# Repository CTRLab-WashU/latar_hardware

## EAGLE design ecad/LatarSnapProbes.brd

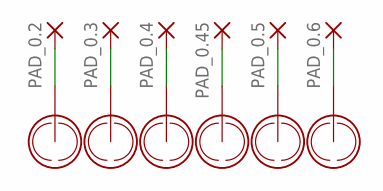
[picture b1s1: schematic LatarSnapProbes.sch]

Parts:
P1: PROBE_0.2_IN
PAD_0.2, PAD_0.3, PAD_0.4, PAD_0.5, PAD_0.6, PAD_0.45: SMD5; SMD2,54-5,08
U$1: PROBE_0.4_IN
U$3: PROBE_0.3_IN
U$4: PROBE_0.45_IN
U$5: PROBE_0.5_IN
U$6: PROBE_0.6_IN

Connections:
unnamed: P1.P1, P1.P2, PAD_0.2.1
unnamed: PAD_0.3.1, U$3.P1, U$3.P2
unnamed: PAD_0.4.1, U$1.P1, U$1.P2
unnamed: PAD_0.45.1, U$4.P1, U$4.P2
unnamed: PAD_0.5.1, U$5.P1, U$5.P2
unnamed: PAD_0.6.1, U$6.P1, U$6.P2

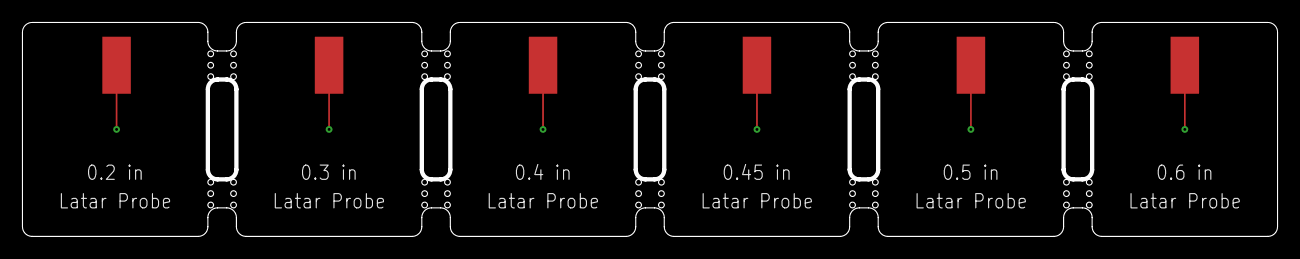
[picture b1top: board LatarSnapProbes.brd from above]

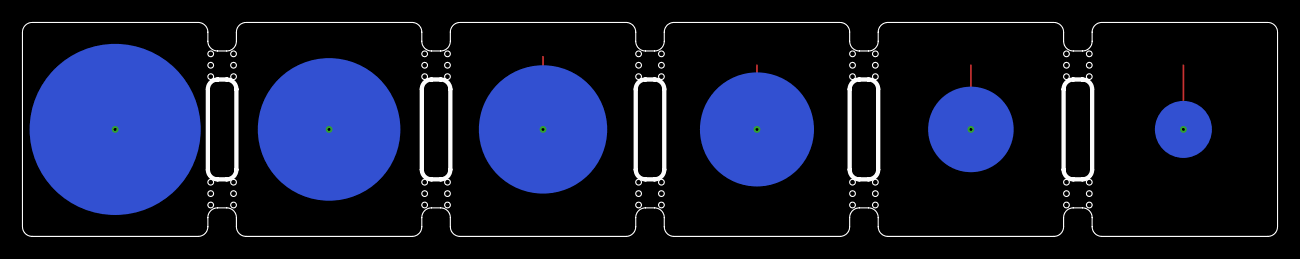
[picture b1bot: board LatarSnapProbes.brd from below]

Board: 2 copper layers, 111.8 x 19.1 mm, 12 parts (6 on the bottom side), 6 nets.

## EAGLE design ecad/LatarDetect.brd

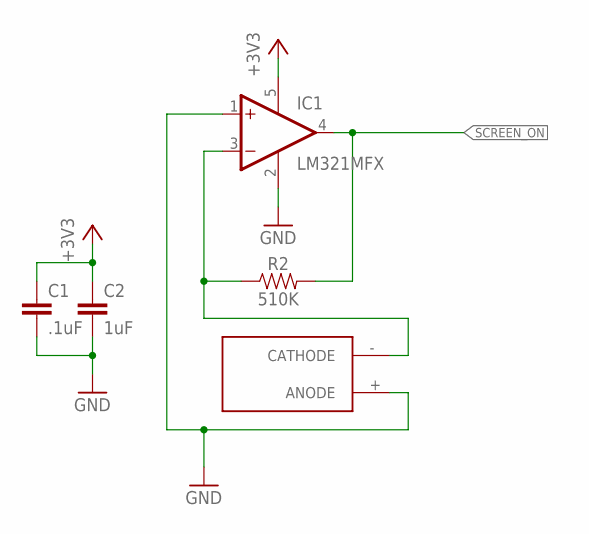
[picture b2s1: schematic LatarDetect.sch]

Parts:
C1: .1uF; C0805
C2: 1uF; C0805
IC1: LM321MFX; SOT23-5
R2: 510K; 0805
U$1: BPW34S-Z

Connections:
+3V3: C1.1, C2.1, IC1.5 (V+)
GND: C1.2, C2.2, IC1.1 (+IN), IC1.2 (V-), U$1.+ (ANODE)
unnamed: IC1.3 (-IN), R2.1, U$1.- (CATHODE)
SCREEN_ON: IC1.4 (OUT), R2.2

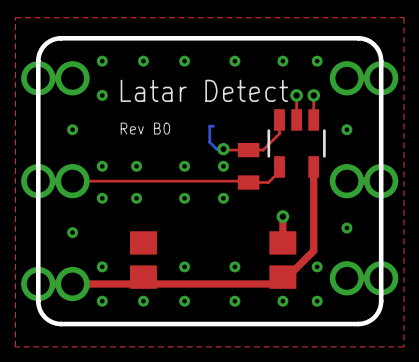
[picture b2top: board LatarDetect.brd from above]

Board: 2 copper layers, 19.1 x 15.9 mm, 5 parts (1 on the bottom side), 4 nets.

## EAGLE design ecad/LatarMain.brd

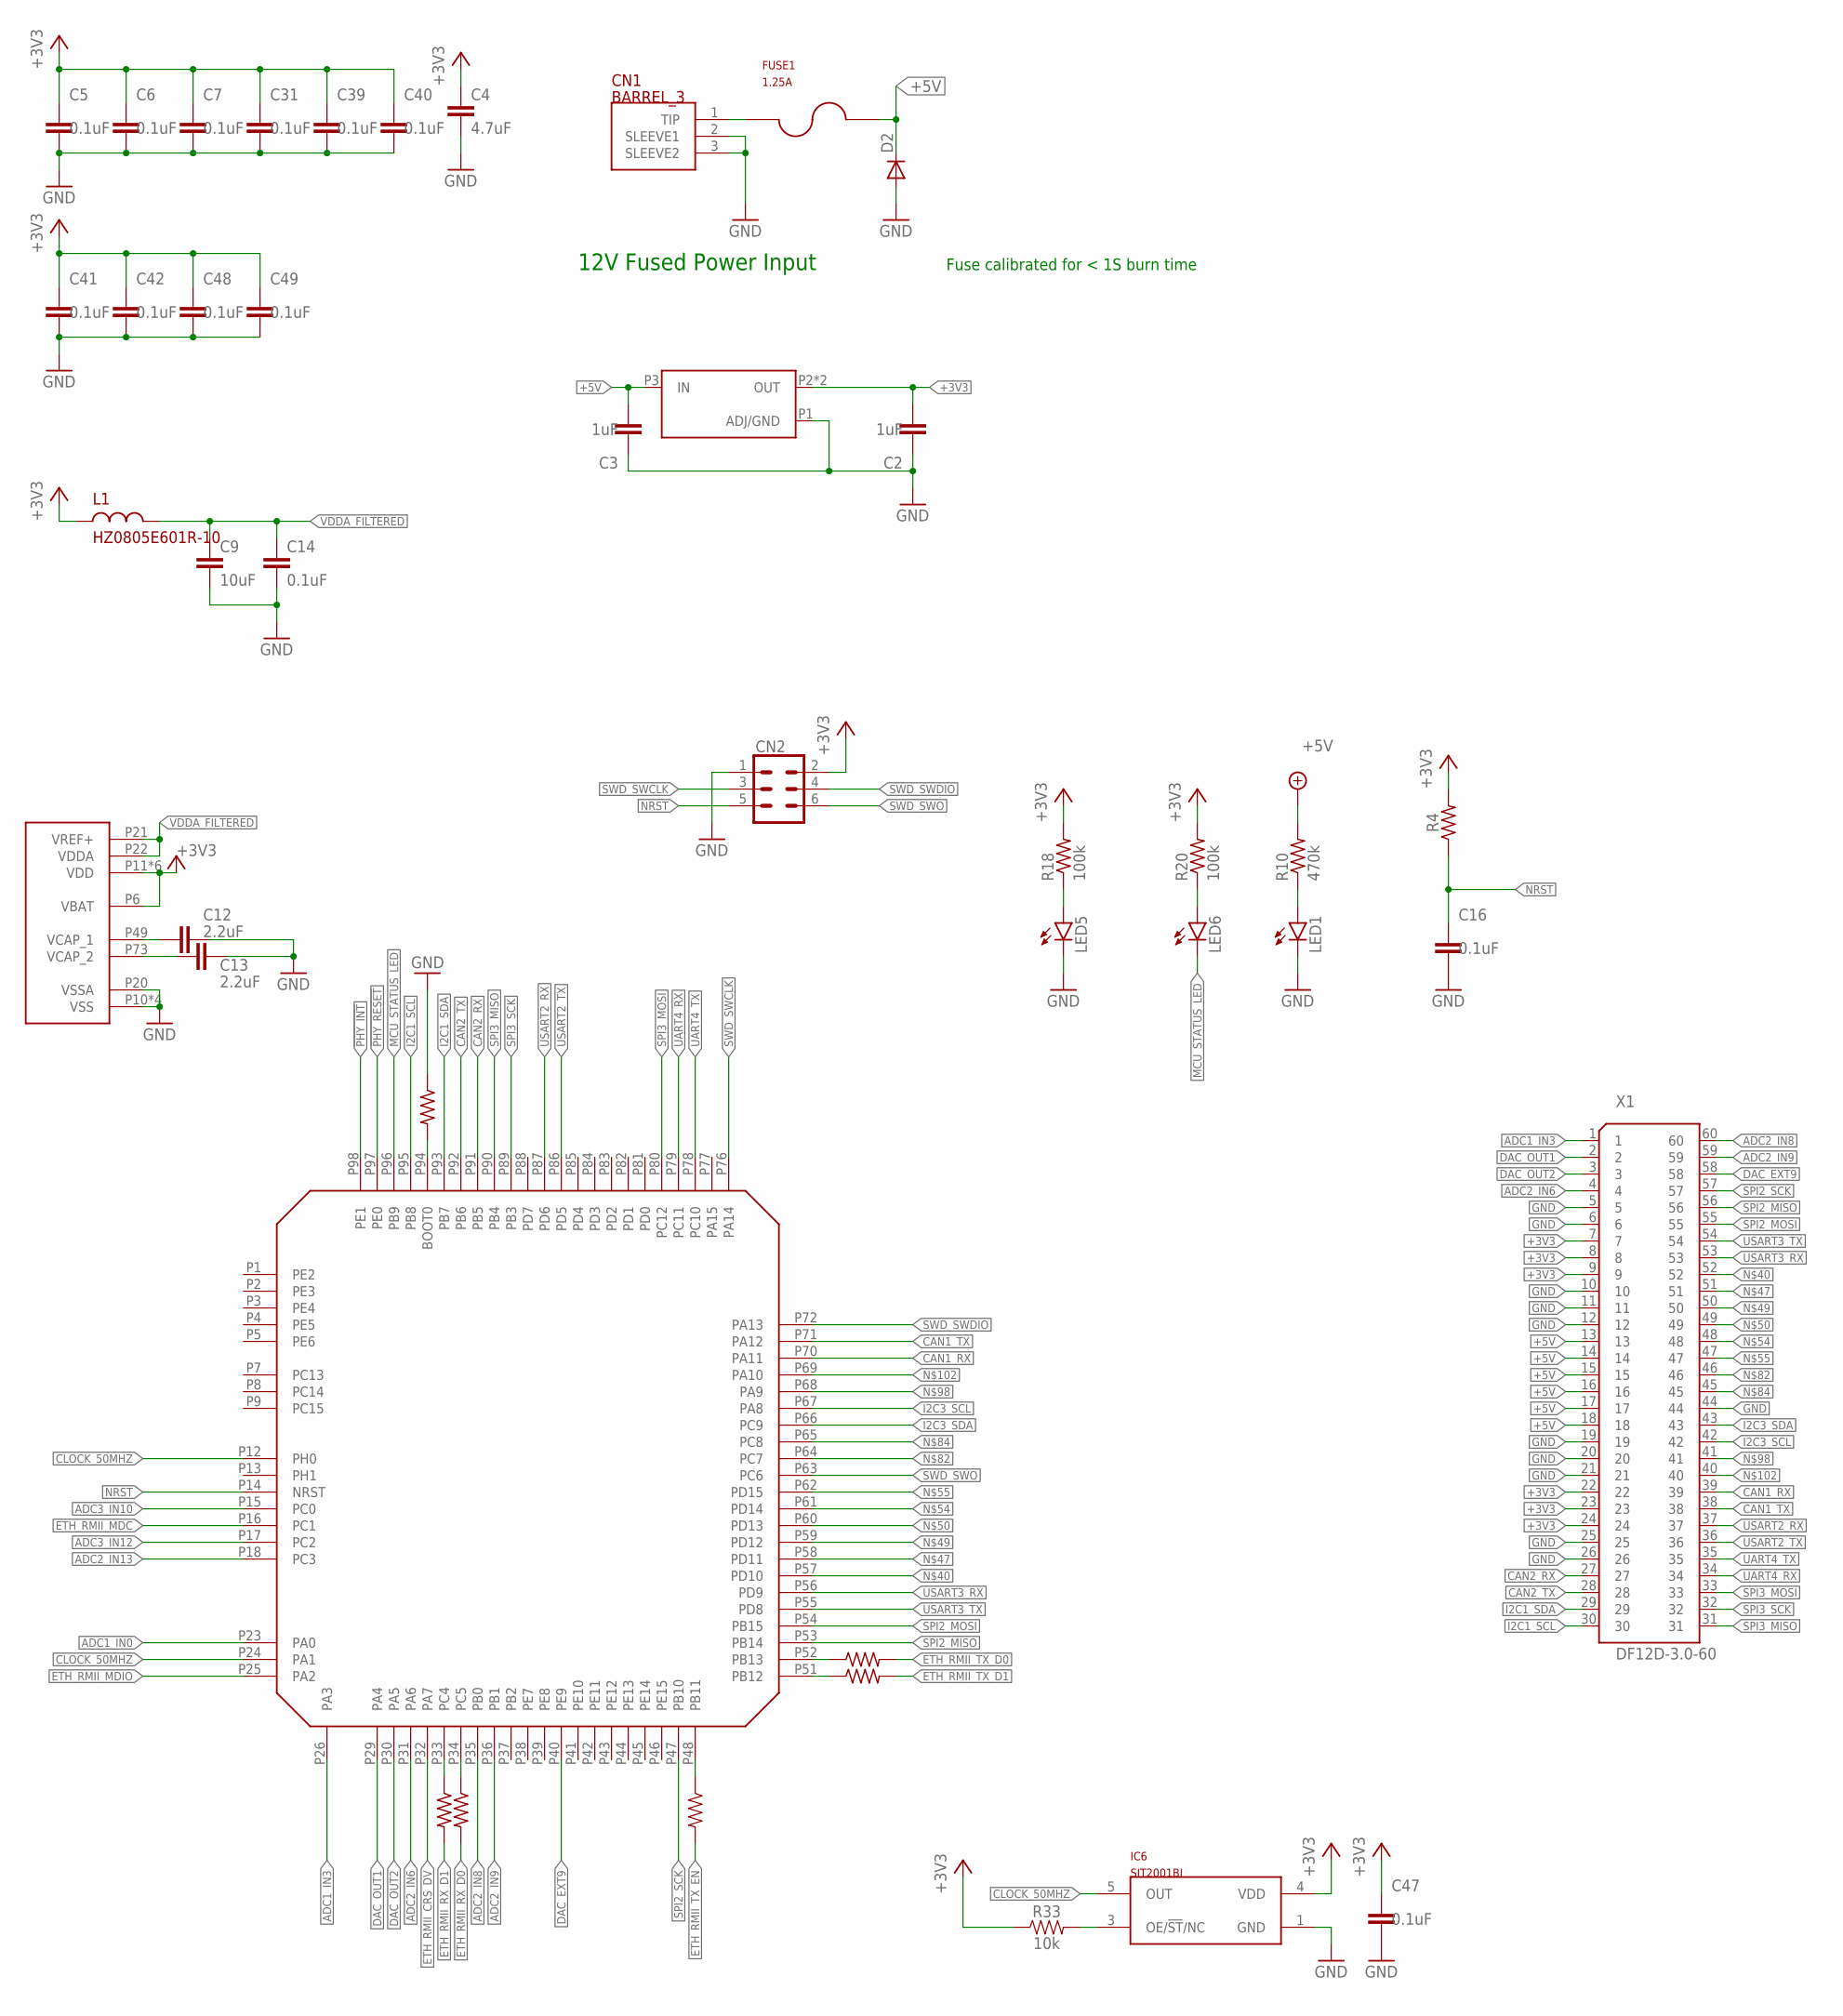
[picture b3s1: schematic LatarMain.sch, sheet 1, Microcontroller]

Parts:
C2, C3: 1uF; C1206
C4: 4.7uF; C0805
C5, C6, C7, C16, C31, C39, C40, C41, C42, C47, C48, C49: 0.1uF; C0603
C9: 10uF; C0805
C12, C13: 2.2uF; C0805
C14: 0.1uF; C0805
CN1: BARREL_3; PJ-002AH
CN2: CONN_03X22X3_SILK_MALE_PTH; 2X3
D2: DIODE-DO214AC; DO214AC
FUSE1: 1.25A; BEL_FUSE_2SMD
IC6: SIT2001BI; SOT23-5
L1: HZ0805E601R-10; R0805
LED1, LED5, LED6: LEDCHIPLED_0603; CHIPLED_0603
R4, R34: 10k; R0805
R10: 470k; R0603
R18, R20: 100k; R0603
R32, R39, R40, R41: 50k; R0402
R33: 10k; 0805
R42: 50k; 0603
U$1: AZ1117E; SOT-223
U$2: STM32_F407_LQFP100; STM32_LQFP100
X1: DF12D-3.0-60; DF12-3.0-60

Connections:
!PHY_INT: U$2.P98 (PE1); also elsewhere on the board
!PHY_RESET: U$2.P97 (PE0); also elsewhere on the board
+3V3: C2.2, C4.1, C5.1, C6.1, C7.1, C31.1, C39.1, C40.1, C41.1, C42.1, C47.1, C48.1, C49.1, CN2.2, IC6.4 (VDD), L1.1, R4.2, R18.2, R20.2, R33.1, U$1.P2 (OUT), U$1.TAB (OUT), U$2.P6 (VBAT), U$2.P11 (VDD), U$2.P19 (VDD), U$2.P28 (VDD), U$2.P50 (VDD), U$2.P75 (VDD), U$2.P100 (VDD), X1.7, X1.8, X1.9, X1.22, X1.23, X1.24; also elsewhere on the board
+5V: C3.2, D2.C, FUSE1.2, R10.2, U$1.P3 (IN), X1.13, X1.14, X1.15, X1.16, X1.17, X1.18
ADC1_IN0: U$2.P23 (PA0)
ADC1_IN3: U$2.P26 (PA3), X1.1
ADC2_IN6: U$2.P31 (PA6), X1.4
ADC2_IN8: U$2.P35 (PB0), X1.60
ADC2_IN9: U$2.P36 (PB1), X1.59
ADC2_IN13: U$2.P18 (PC3)
ADC3_IN10: U$2.P15 (PC0)
ADC3_IN12: U$2.P17 (PC2)
CAN1_RX: U$2.P70 (PA11), X1.39
CAN1_TX: U$2.P71 (PA12), X1.38
CAN2_RX: U$2.P91 (PB5), X1.27
CAN2_TX: U$2.P92 (PB6), X1.28
CLOCK_50MHZ: IC6.5 (OUT), U$2.P12 (PH0), U$2.P24 (PA1); also elsewhere on the board
DAC_EXT9: U$2.P40 (PE9), X1.58
DAC_OUT1: U$2.P29 (PA4), X1.2
DAC_OUT2: U$2.P30 (PA5), X1.3
ETH_RMII_CRS_DV: U$2.P32 (PA7); also elsewhere on the board
ETH_RMII_MDC: U$2.P16 (PC1); also elsewhere on the board
ETH_RMII_MDIO: U$2.P25 (PA2); also elsewhere on the board
ETH_RMII_RX_D0: R32.2
ETH_RMII_RX_D1: R39.2
ETH_RMII_TX_D0: R40.2; also elsewhere on the board
ETH_RMII_TX_D1: R41.2; also elsewhere on the board
ETH_RMII_TX_EN: R42.2; also elsewhere on the board
GND: C2.1, C3.1, C4.2, C5.2, C6.2, C7.2, C9.2, C12.2, C13.2, C14.2, C16.2, C31.2, C39.2, C40.2, C41.2, C42.2, C47.2, C48.2, C49.2, CN1.2 (SLEEVE1), CN1.3 (SLEEVE2), CN2.1, D2.A, IC6.1 (GND), LED1.C, LED5.C, R34.1, U$1.P1 (ADJ/GND), U$2.P10 (VSS), U$2.P20 (VSSA), U$2.P27 (VSS), U$2.P74 (VSS), U$2.P99 (VSS), X1.5, X1.6, X1.10, X1.11, X1.12, X1.19, X1.20, X1.21, X1.25, X1.26, X1.44; also elsewhere on the board
I2C1_SCL: U$2.P95 (PB8), X1.30
I2C1_SDA: U$2.P93 (PB7), X1.29
I2C3_SCL: U$2.P67 (PA8), X1.42
I2C3_SDA: U$2.P66 (PC9), X1.43
MCU_STATUS_LED: LED6.C, U$2.P96 (PB9)
unnamed: R39.1, U$2.P33 (PC4)
unnamed: C12.1, U$2.P49 (VCAP_1)
unnamed: C13.1, U$2.P73 (VCAP_2)
unnamed: R40.1, U$2.P52 (PB13)
unnamed: LED1.A, R10.1
unnamed: R34.2, U$2.P94 (BOOT0)
unnamed: IC6.3 (OE/!ST!/NC), R33.2
unnamed: CN1.1 (TIP), FUSE1.1
unnamed: R32.1, U$2.P34 (PC5)
unnamed: R41.1, U$2.P51 (PB12)
unnamed: R42.1, U$2.P48 (PB11)
unnamed: U$2.P57 (PD10), X1.52
unnamed: U$2.P58 (PD11), X1.51
unnamed: LED6.A, R20.1
unnamed: U$2.P59 (PD12), X1.50
unnamed: U$2.P60 (PD13), X1.49
unnamed: U$2.P61 (PD14), X1.48
unnamed: U$2.P62 (PD15), X1.47
unnamed: U$2.P64 (PC7), X1.46
unnamed: U$2.P65 (PC8), X1.45
unnamed: U$2.P68 (PA9), X1.41
unnamed: U$2.P69 (PA10), X1.40
unnamed: LED5.A, R18.1
NRST: C16.1, CN2.5, R4.1, U$2.P14 (NRST)
SPI2_MISO: U$2.P53 (PB14), X1.56
SPI2_MOSI: U$2.P54 (PB15), X1.55
SPI2_SCK: U$2.P47 (PB10), X1.57
SPI3_MISO: U$2.P90 (PB4), X1.31
SPI3_MOSI: U$2.P80 (PC12), X1.33
SPI3_SCK: U$2.P89 (PB3), X1.32
SWD_SWCLK: CN2.3, U$2.P76 (PA14)
SWD_SWDIO: CN2.4, U$2.P72 (PA13)
SWD_SWO: CN2.6, U$2.P63 (PC6)
UART4_RX: U$2.P79 (PC11), X1.34
UART4_TX: U$2.P78 (PC10), X1.35
USART2_RX: U$2.P87 (PD6), X1.37
USART2_TX: U$2.P86 (PD5), X1.36
USART3_RX: U$2.P56 (PD9), X1.53
USART3_TX: U$2.P55 (PD8), X1.54
VDDA_FILTERED: C9.1, C14.1, L1.2, U$2.P21 (VREF+), U$2.P22 (VDDA)

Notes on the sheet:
12V Fused Power Input
Fuse calibrated for < 1S burn time

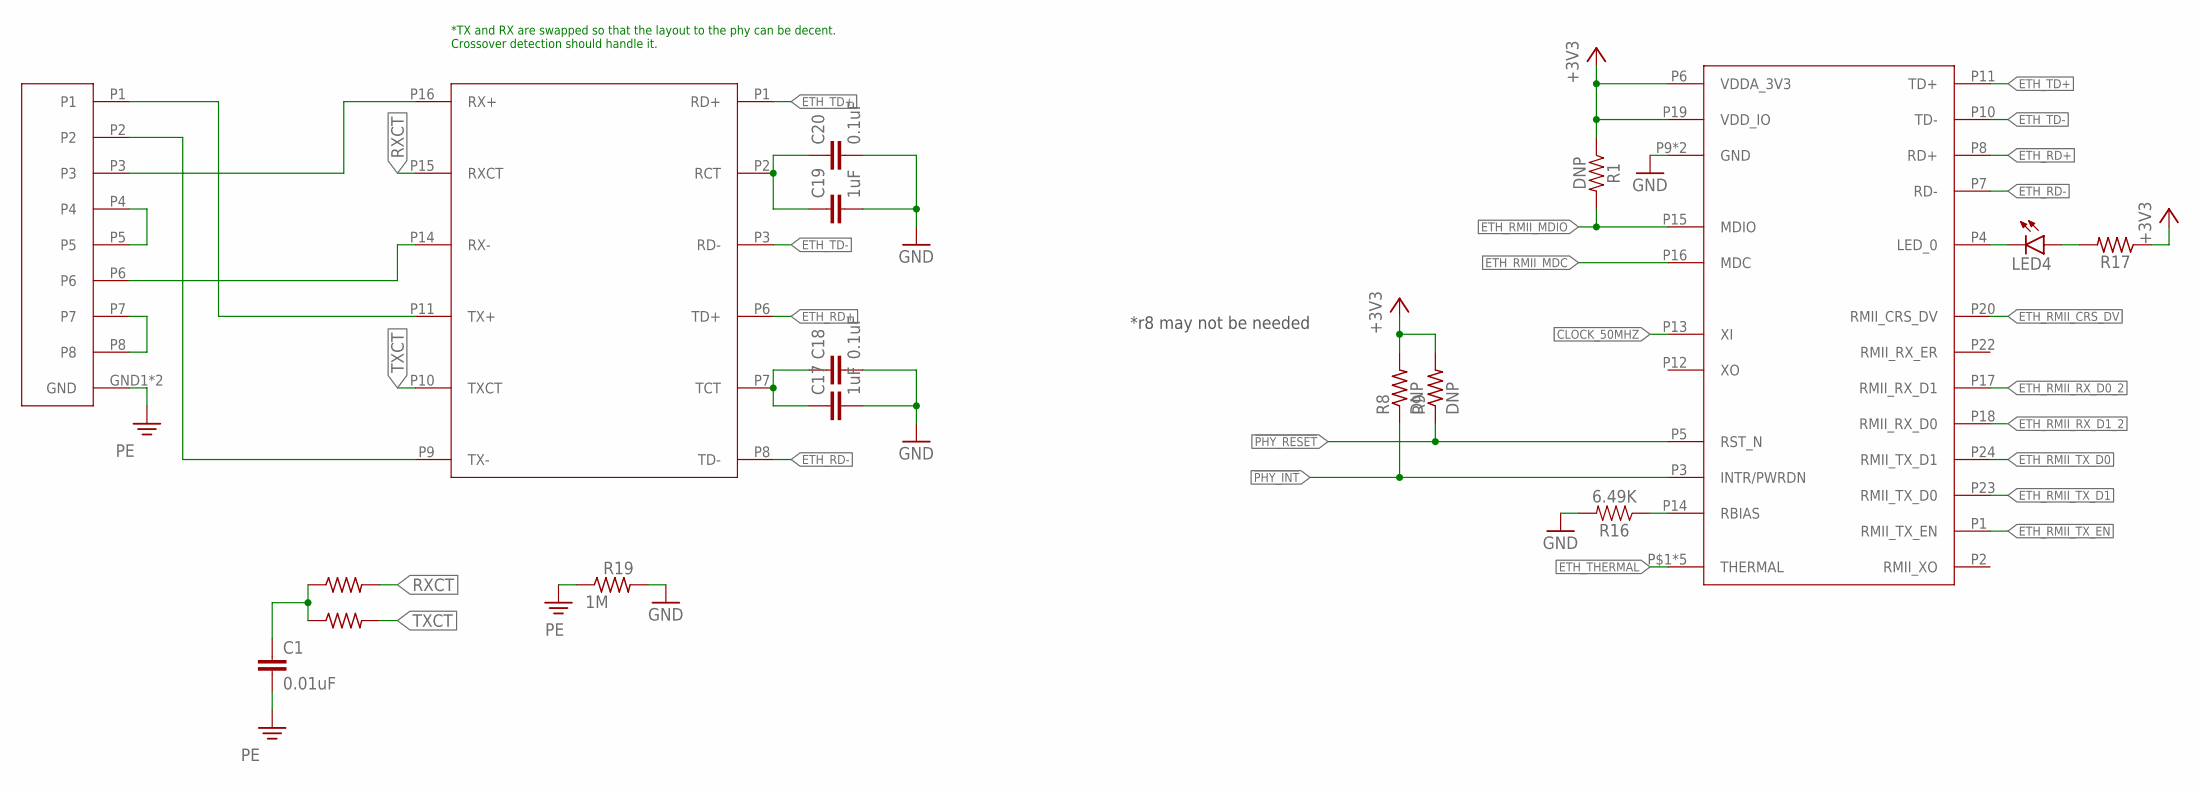
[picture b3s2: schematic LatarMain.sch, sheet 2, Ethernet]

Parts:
C1: 0.01uF; C0805
C17, C19: 1uF; C0805
C18, C20: 0.1uF; C0805
LED4: LEDCHIP-LED0603; CHIP-LED0603
R1: DNP; 0603
R2, R5: 75R; R0805
R8, R9: DNP; R0603
R16: 6.49K; 0603
R17: 100k; R0603
R19: 1M; R1206
U$15: 749013011
U$16: A120645-ND
U$17: DP83825I

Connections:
!PHY_INT: R8.1, U$17.P3 (INTR/PWRDN); also elsewhere on the board
!PHY_RESET: R9.1, U$17.P5 (RST_N); also elsewhere on the board
+3V3: R1.1, R8.2, R9.2, R17.1, U$17.P6 (VDDA_3V3), U$17.P19 (VDD_IO); also elsewhere on the board
CLOCK_50MHZ: U$17.P13 (XI); also elsewhere on the board
ETH_RD+: U$15.P6 (TD+), U$17.P8 (RD+)
ETH_RD-: U$15.P8 (TD-), U$17.P7 (RD-)
ETH_RMII_CRS_DV: U$17.P20 (RMII_CRS_DV); also elsewhere on the board
ETH_RMII_MDC: U$17.P16 (MDC); also elsewhere on the board
ETH_RMII_MDIO: R1.2, U$17.P15 (MDIO); also elsewhere on the board
ETH_RMII_RX_D0_2: U$17.P17 (RMII_RX_D1)
ETH_RMII_RX_D1_2: U$17.P18 (RMII_RX_D0)
ETH_RMII_TX_D0: U$17.P24 (RMII_TX_D1); also elsewhere on the board
ETH_RMII_TX_D1: U$17.P23 (RMII_TX_D0); also elsewhere on the board
ETH_RMII_TX_EN: U$17.P1 (RMII_TX_EN); also elsewhere on the board
ETH_TD+: U$15.P1 (RD+), U$17.P11 (TD+)
ETH_TD-: U$15.P3 (RD-), U$17.P10 (TD-)
ETH_THERMAL: U$17.P$1 (THERMAL), U$17.P$2 (THERMAL), U$17.P$3 (THERMAL), U$17.P$4 (THERMAL), U$17.PT (THERMAL)
GND: C17.2, C18.2, C19.2, C20.2, R16.2, R19.2, U$17.P9 (GND), U$17.P21 (GND); also elsewhere on the board
GND_EARTH: C1.2, R19.1, U$16.GND1 (GND), U$16.GND2 (GND)
unnamed: LED4.C, U$17.P4 (LED_0)
unnamed: C19.1, C20.1, U$15.P2 (RCT)
unnamed: C17.1, C18.1, U$15.P7 (TCT)
unnamed: C1.1, R2.1, R5.1
unnamed: U$15.P14 (RX-), U$16.P6
unnamed: U$15.P9 (TX-), U$16.P2
unnamed: U$15.P11 (TX+), U$16.P1
unnamed: U$15.P16 (RX+), U$16.P3
unnamed: U$16.P4, U$16.P5
unnamed: U$16.P7, U$16.P8
unnamed: LED4.A, R17.2
unnamed: R16.1, U$17.P14 (RBIAS)
RXCT: R2.2, U$15.P15 (RXCT)
TXCT: R5.2, U$15.P10 (TXCT)

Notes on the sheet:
*TX and RX are swapped so that the layout to the phy can be decent. Crossover detection should handle it.
*r8 may not be needed

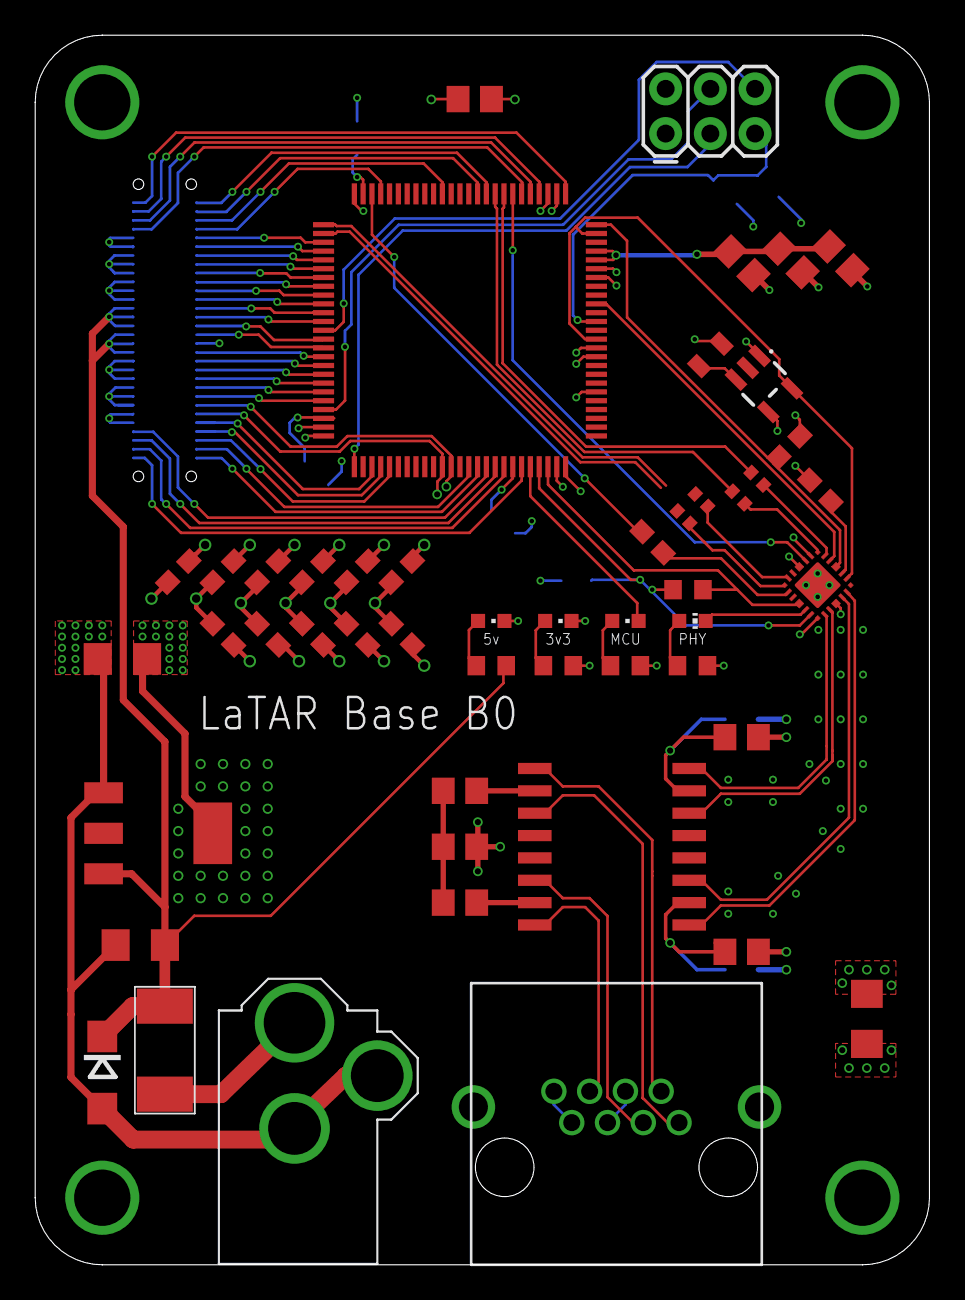
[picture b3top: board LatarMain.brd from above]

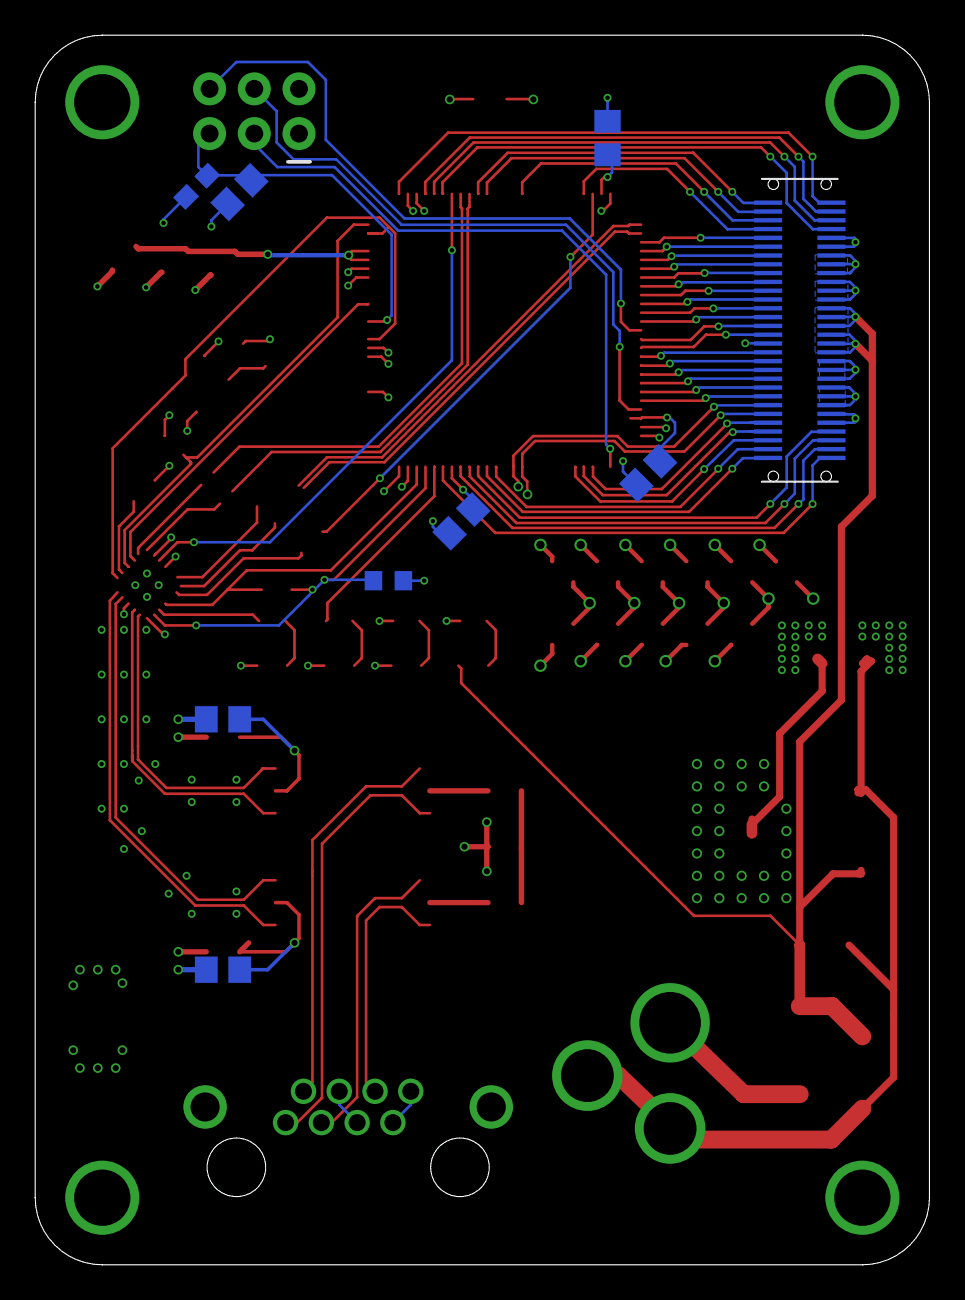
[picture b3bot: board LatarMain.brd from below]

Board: 4 copper layers, 50.8 x 69.8 mm, 59 parts (9 on the bottom side), 88 nets.

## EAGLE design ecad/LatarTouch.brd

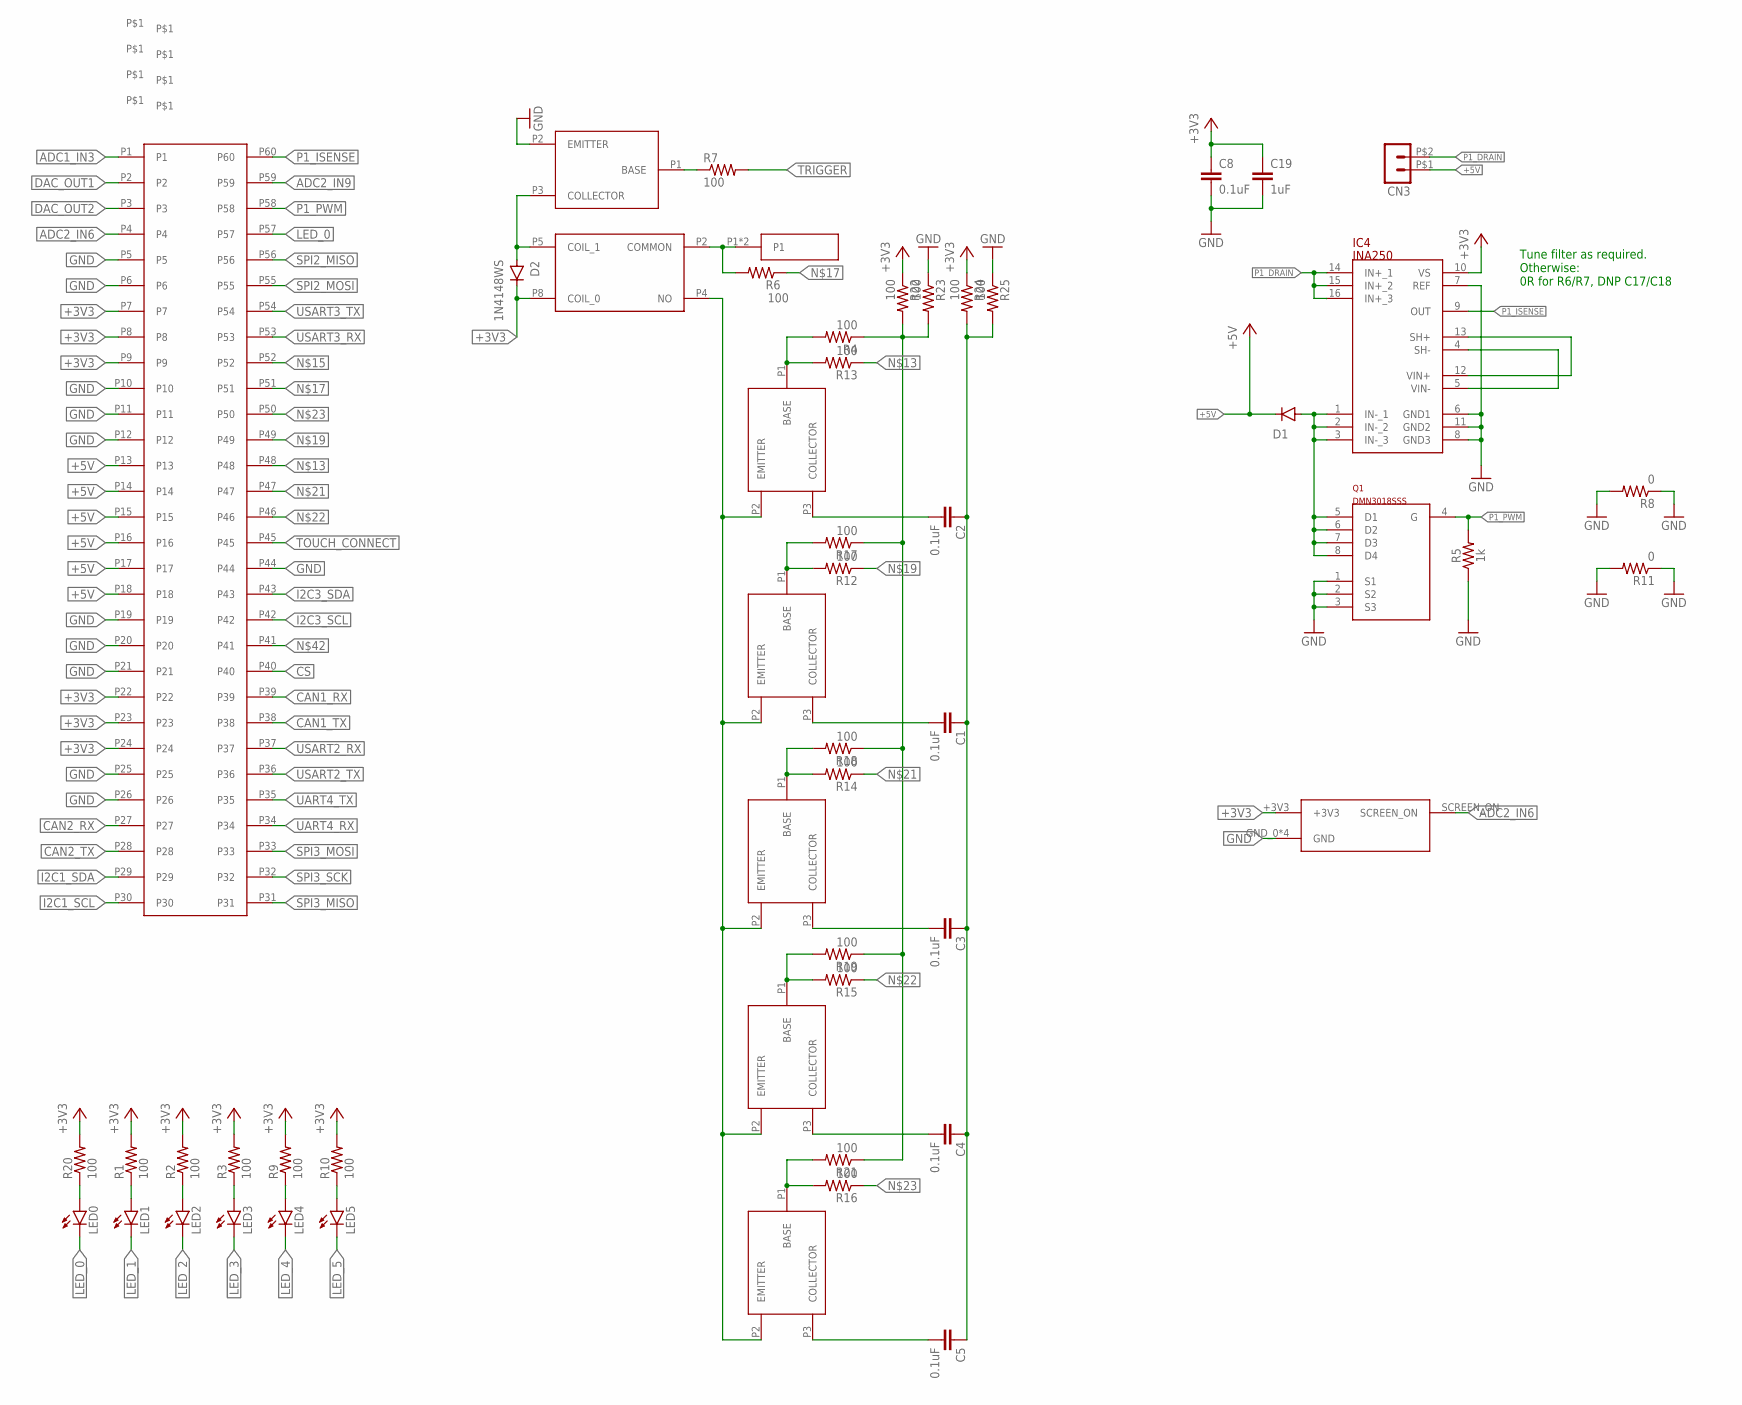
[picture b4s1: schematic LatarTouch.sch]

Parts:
C1, C2, C3, C4, C5: 0.1uF; C0603
C8: 0.1uF; C0805
C19: 1uF; C0805
CN3: HEADER_POS2_43650-0212; 43650-0212
D1: DIODE-DO214AC; DO214AC
D2: 1N4148WS; SOD-323
IC4: INA250; TSSOP16
LED0, LED1, LED2, LED3, LED4, LED5: LEDCHIPLED_0603; CHIPLED_0603
Q1: DMN3018SSS; SO08
R1, R2, R3, R4, R6, R7, R9, R10, R12, R13, R14, R15, R16, R17, R18, R19, R20, R21, R22, R23, R24, R25: 100; R0603
R5: 1k; 0805
R8: 0; R0603
R11: 0; R1206
U$4: TOUCH; TOUCH_PROBE
U$5, U$15, U$16, U$17, U$18, U$19: MMBT3904; SOT23
U$6: DF12(3.0)-60DS-0.5V(86)
U$7, U$9, U$10, U$11: 9774030360R
U$8: DETECT_DAUGHTER_BOARD
U$14: G6L-1F

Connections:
+3V3: C8.1, C19.1, IC4.10 (VS), R1.2, R2.2, R3.2, R9.2, R10.2, R20.2, R22.1, R24.1, U$6.P7, U$6.P8, U$6.P9, U$6.P22, U$6.P23, U$6.P24, U$8.+3V3
+5V: CN3.P$1 (1), D1.C, U$6.P13, U$6.P14, U$6.P15, U$6.P16, U$6.P17, U$6.P18
ADC1_IN3: U$6.P1
ADC2_IN6: U$6.P4, U$8.SCREEN_ON
ADC2_IN9: U$6.P59
CAN1_RX: U$6.P39
CAN1_TX: U$6.P38
CAN2_RX: U$6.P27
CAN2_TX: U$6.P28
CS: U$6.P40
DAC_OUT1: U$6.P2
DAC_OUT2: U$6.P3
GND: C8.2, C19.2, IC4.6 (GND1), IC4.7 (REF), IC4.8 (GND3), IC4.11 (GND2), Q1.1 (S1), Q1.2 (S2), Q1.3 (S3), R5.1, R8.1, R8.2, R11.1, R11.2, R23.1, R25.1, U$6.P5, U$6.P6, U$6.P10, U$6.P11, U$6.P12, U$6.P19, U$6.P20, U$6.P21, U$6.P25, U$6.P26, U$6.P44, U$8.GND_0 (GND), U$8.GND_1 (GND), U$8.GND_2 (GND), U$8.GND_3 (GND), U$15.P2 (EMITTER)
I2C1_SCL: U$6.P30
I2C1_SDA: U$6.P29
I2C3_SCL: U$6.P42
I2C3_SDA: U$6.P43
LED_0: LED0.C, U$6.P57
LED_1: LED1.C
LED_2: LED2.C
LED_3: LED3.C
LED_4: LED4.C
LED_5: LED5.C
unnamed: R16.2, R21.2, U$19.P1 (BASE)
unnamed: LED1.A, R1.1
unnamed: R15.2, R19.2, U$18.P1 (BASE)
unnamed: R14.2, R18.2, U$17.P1 (BASE)
unnamed: R12.2, R17.2, U$16.P1 (BASE)
unnamed: R6.2, U$4.P1, U$4.P2, U$14.P2 (COMMON)
unnamed: LED3.A, R3.1
unnamed: D1.A, IC4.1 (IN-_1), IC4.2 (IN-_2), IC4.3 (IN-_3), Q1.5 (D1), Q1.6 (D2), Q1.7 (D3), Q1.8 (D4)
unnamed: IC4.4 (SH-), IC4.5 (VIN-)
unnamed: R4.2, R13.2, U$5.P1 (BASE)
unnamed: IC4.12 (VIN+), IC4.13 (SH+)
unnamed: LED2.A, R2.1
unnamed: R13.1, U$6.P48
unnamed: U$5.P2 (EMITTER), U$14.P4 (NO), U$16.P2 (EMITTER), U$17.P2 (EMITTER), U$18.P2 (EMITTER), U$19.P2 (EMITTER)
unnamed: D2.A, U$14.P5 (COIL_1), U$15.P3 (COLLECTOR)
unnamed: R6.1, U$6.P51
unnamed: D2.C, U$14.P8 (COIL_0)
unnamed: R12.1, U$6.P49
unnamed: R14.1, U$6.P47
unnamed: R15.1, U$6.P46
unnamed: R16.1, U$6.P50
unnamed: R7.1, U$15.P1 (BASE)
unnamed: LED4.A, R9.1
unnamed: LED5.A, R10.1
unnamed: R4.1, R17.1, R18.1, R19.1, R21.1, R22.2, R23.2
unnamed: C1.1, C2.1, C3.1, C4.1, C5.1, R24.2, R25.2
unnamed: C5.2, U$19.P3 (COLLECTOR)
unnamed: C4.2, U$18.P3 (COLLECTOR)
unnamed: C3.2, U$17.P3 (COLLECTOR)
unnamed: C1.2, U$16.P3 (COLLECTOR)
unnamed: C2.2, U$5.P3 (COLLECTOR)
unnamed: LED0.A, R20.1
P1_DRAIN: CN3.P$2 (2), IC4.14 (IN+_1), IC4.15 (IN+_2), IC4.16 (IN+_3)
P1_ISENSE: IC4.9 (OUT), U$6.P60
P1_PWM: Q1.4 (G), R5.2, U$6.P58
SPI2_MISO: U$6.P56
SPI2_MOSI: U$6.P55
SPI3_MISO: U$6.P31
SPI3_MOSI: U$6.P33
SPI3_SCK: U$6.P32
TOUCH_CONNECT: U$6.P45
TRIGGER: R7.2
UART4_RX: U$6.P34
UART4_TX: U$6.P35
USART2_RX: U$6.P37
USART2_TX: U$6.P36
USART3_RX: U$6.P53
USART3_TX: U$6.P54

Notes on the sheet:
Tune filter as required. Otherwise: 0R for R6/R7, DNP C17/C18

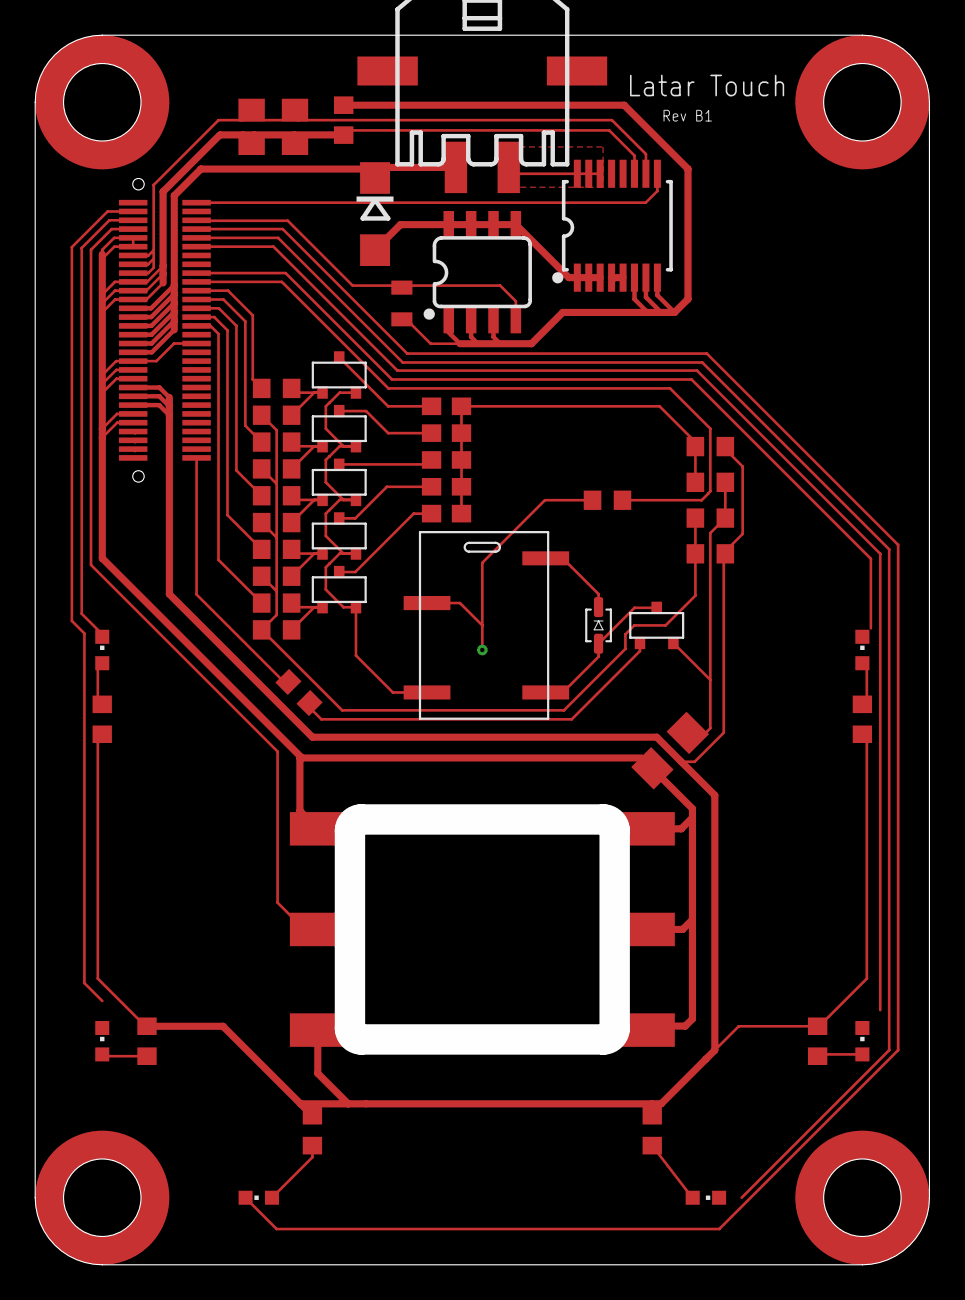
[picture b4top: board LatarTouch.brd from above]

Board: 2 copper layers, 50.8 x 69.8 mm, 57 parts (1 on the bottom side), 40 nets.

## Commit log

2021-02-04 add sch and brd files
2021-02-04 add images for easy viewing
2021-02-04 add probes

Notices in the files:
parts and their libraries:
SparkFun-Resistors: Licensing: Creative Commons ShareAlike 4.0 International - https://creativecommons.org/licenses/by-sa/4.0
